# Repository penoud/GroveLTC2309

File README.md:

# GroveLTC2309
A Grove i2c 8 channels ADC ŵith amplifier for each channel

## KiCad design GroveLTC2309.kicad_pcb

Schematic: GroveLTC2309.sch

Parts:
P1, P2, P3, P4, P5, P6, P7, P8, P9: CONN_4_GROVE
R29, R30, R31, R32: 4.7K

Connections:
+5V: P1.3, P2.3, P3.3, P4.3, P5.3, P6.3, P7.3, P8.3, P9.3, R29.1, R30.1, R31.1, R32.1; also elsewhere on the board
/ADC/SCL: R32.2; also elsewhere on the board
/ADC/SDA: R31.2; also elsewhere on the board
/Amplifier1/IN0: P1.1; also elsewhere on the board
/Amplifier1/IN1: P2.1; also elsewhere on the board
/Amplifier1/IN2: P3.1; also elsewhere on the board
/Amplifier1/IN3: P4.1; also elsewhere on the board
/Amplifier2/IN0: P5.1; also elsewhere on the board
/Amplifier2/IN1: P6.1; also elsewhere on the board
/Amplifier2/IN2: P7.1; also elsewhere on the board
/Amplifier2/IN3: P8.1; also elsewhere on the board
/TCA9517A/SCL_B: P9.1, R29.2; also elsewhere on the board
/TCA9517A/SDA_B: P9.2, R30.2; also elsewhere on the board
GND: P1.4, P2.4, P3.4, P4.4, P5.4, P6.4, P7.4, P8.4, P9.4; also elsewhere on the board

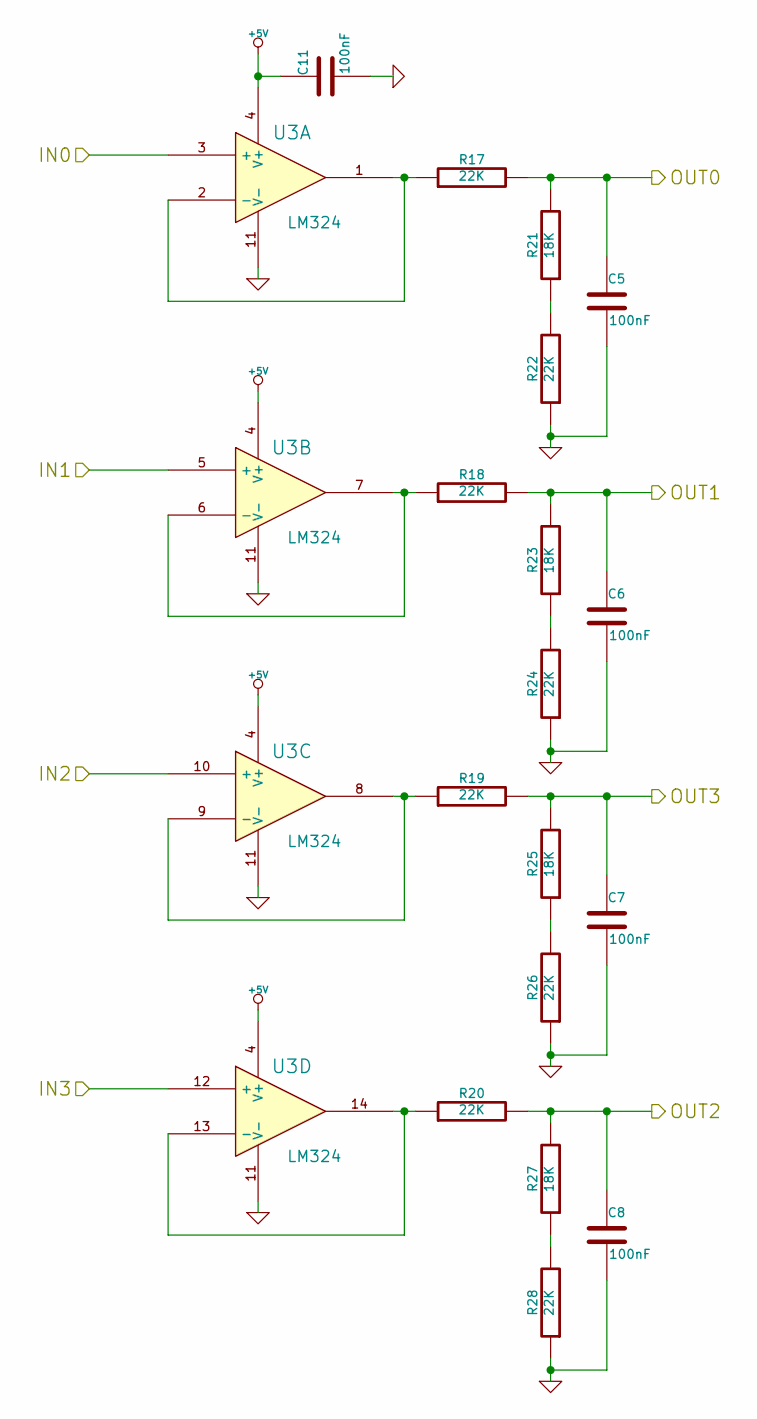
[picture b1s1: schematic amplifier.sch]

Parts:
C1, C2, C3, C4, C9: 100nF
R1, R2, R3, R4, R6, R8, R10, R12: 22K
R5, R7, R9, R11: 18K
U1: LM324

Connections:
+5V: C9.1, U1.4 (V+); also elsewhere on the board
/ADC/CH4: C1.1, R1.2, R5.2; also elsewhere on the board
/ADC/CH5: C2.1, R2.2, R7.2; also elsewhere on the board
/ADC/CH6: C4.1, R4.2, R11.2; also elsewhere on the board
/ADC/CH7: C3.1, R3.2, R9.2; also elsewhere on the board
/Amplifier2/IN0: U1.3 (+); also elsewhere on the board
/Amplifier2/IN1: U1.5 (+); also elsewhere on the board
/Amplifier2/IN2: U1.10 (+); also elsewhere on the board
/Amplifier2/IN3: U1.12 (+); also elsewhere on the board
GND: C1.2, C2.2, C3.2, C4.2, C9.2, R6.1, R8.1, R10.1, R12.1, U1.11 (V-); also elsewhere on the board
unnamed: R3.1, U1.8, U1.9 (-)
unnamed: R9.1, R10.2
unnamed: R4.1, U1.13 (-), U1.14
unnamed: R11.1, R12.2
unnamed: R5.1, R6.2
unnamed: R2.1, U1.6 (-), U1.7
unnamed: R1.1, U1.1, U1.2 (-)
unnamed: R7.1, R8.2

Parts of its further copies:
C5, C8, C11: 100nF
R17, R18, R19, R20, R22, R24, R26, R28: 22K
R21, R23, R25, R27: 18K
U3: LM324

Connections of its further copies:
+5V: C11.1, U3.4 (V+); also elsewhere on the board
/ADC/CH0: C5.1, R17.2, R21.2; also elsewhere on the board
/ADC/CH1: R18.2, R23.2; also elsewhere on the board
/ADC/CH2: C8.1, R20.2, R27.2; also elsewhere on the board
/ADC/CH3: R19.2, R25.2; also elsewhere on the board
/Amplifier1/IN0: U3.3 (+); also elsewhere on the board
/Amplifier1/IN1: U3.5 (+); also elsewhere on the board
/Amplifier1/IN2: U3.10 (+); also elsewhere on the board
/Amplifier1/IN3: U3.12 (+); also elsewhere on the board
GND: C5.2, C8.2, C11.2, R22.1, R24.1, R26.1, R28.1, U3.11 (V-); also elsewhere on the board
unnamed: R19.1, U3.8, U3.9 (-)
unnamed: R25.1, R26.2
unnamed: R20.1, U3.13 (-), U3.14
unnamed: R27.1, R28.2
unnamed: R21.1, R22.2
unnamed: R18.1, U3.6 (-), U3.7
unnamed: R17.1, U3.1, U3.2 (-)
unnamed: R23.1, R24.2

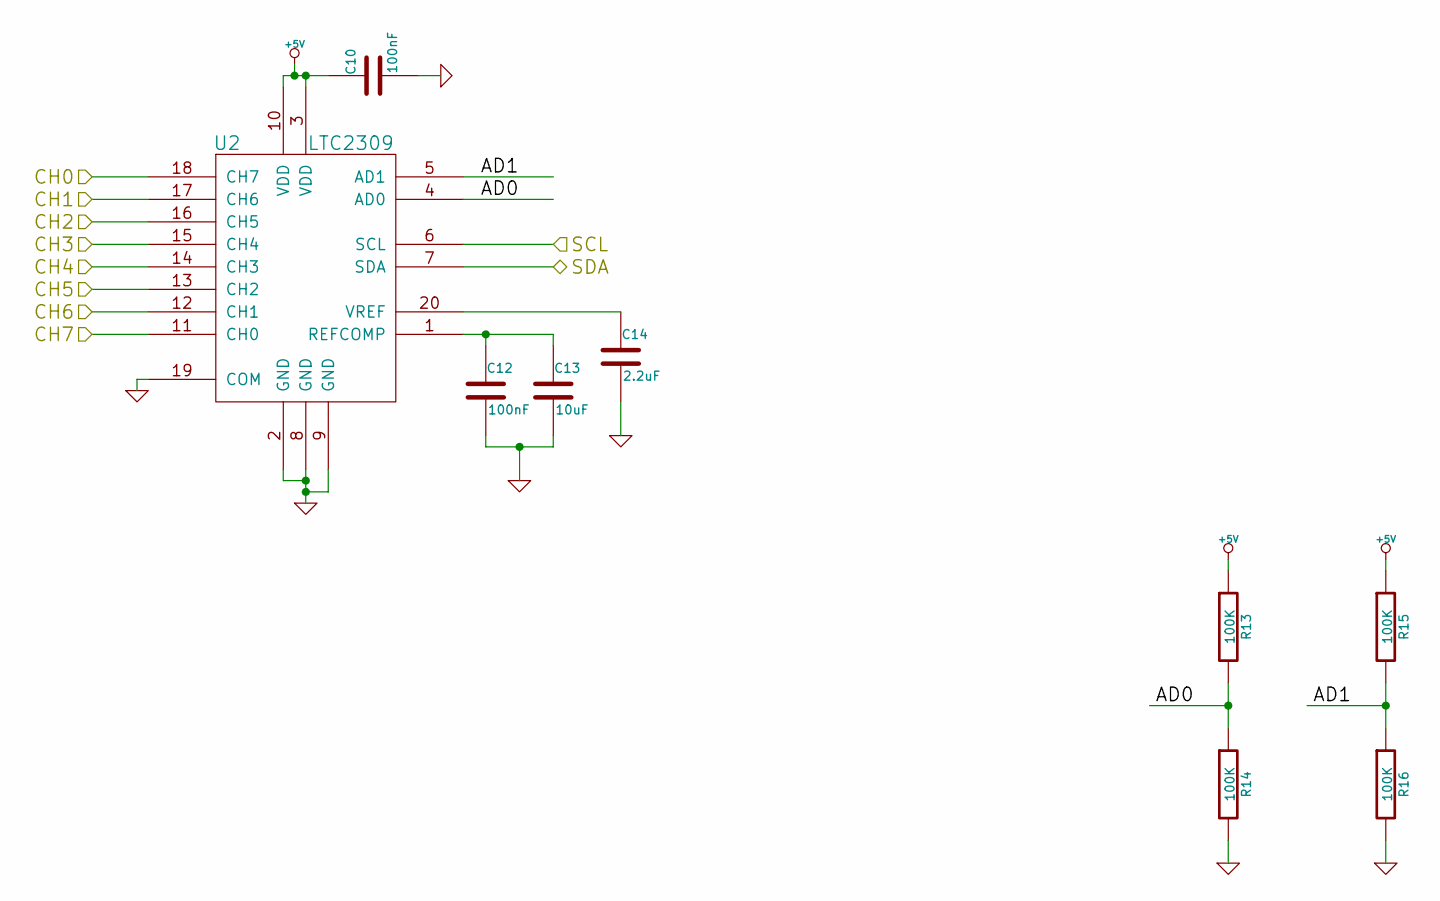
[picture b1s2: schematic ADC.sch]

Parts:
C10, C12: 100nF
C13: 10uF
C14: 2.2uF
R13, R14, R15, R16: 100K
U2: LTC2309

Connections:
+5V: C10.1, R13.1, R15.1, U2.3 (VDD), U2.10 (VDD); also elsewhere on the board
/ADC/AD0: R13.2, R14.1, U2.4 (AD0)
/ADC/AD1: R15.2, R16.1, U2.5 (AD1)
/ADC/CH0: U2.18 (CH7); also elsewhere on the board
/ADC/CH1: U2.17 (CH6); also elsewhere on the board
/ADC/CH2: U2.16 (CH5); also elsewhere on the board
/ADC/CH3: U2.15 (CH4); also elsewhere on the board
/ADC/CH4: U2.14 (CH3); also elsewhere on the board
/ADC/CH5: U2.13 (CH2); also elsewhere on the board
/ADC/CH6: U2.12 (CH1); also elsewhere on the board
/ADC/CH7: U2.11 (CH0); also elsewhere on the board
/ADC/SCL: U2.6 (SCL); also elsewhere on the board
/ADC/SDA: U2.7 (SDA); also elsewhere on the board
GND: C10.2, C12.2, C13.2, C14.2, R14.2, R16.2, U2.2 (GND), U2.8 (GND), U2.9 (GND), U2.19 (COM); also elsewhere on the board
unnamed: C14.1, U2.20 (VREF)
unnamed: C12.1, C13.1, U2.1 (REFCOMP)

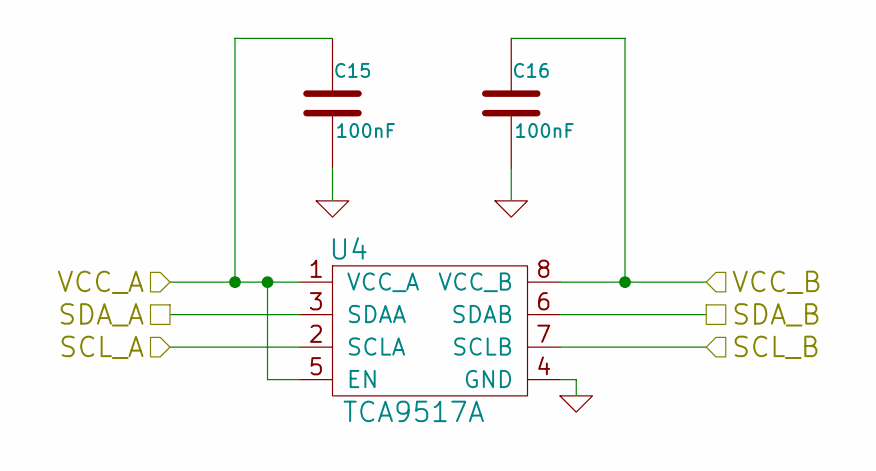
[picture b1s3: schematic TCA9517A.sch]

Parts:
C15, C16: 100nF
U4: TCA9517A

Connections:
+5V: C15.1, C16.1, U4.1 (VCC_A), U4.5 (EN), U4.8 (VCC_B); also elsewhere on the board
/ADC/SCL: U4.2 (SCLA); also elsewhere on the board
/ADC/SDA: U4.3 (SDAA); also elsewhere on the board
/TCA9517A/SCL_B: U4.7 (SCLB); also elsewhere on the board
/TCA9517A/SDA_B: U4.6 (SDAB); also elsewhere on the board
GND: C15.2, C16.2, U4.4 (GND); also elsewhere on the board

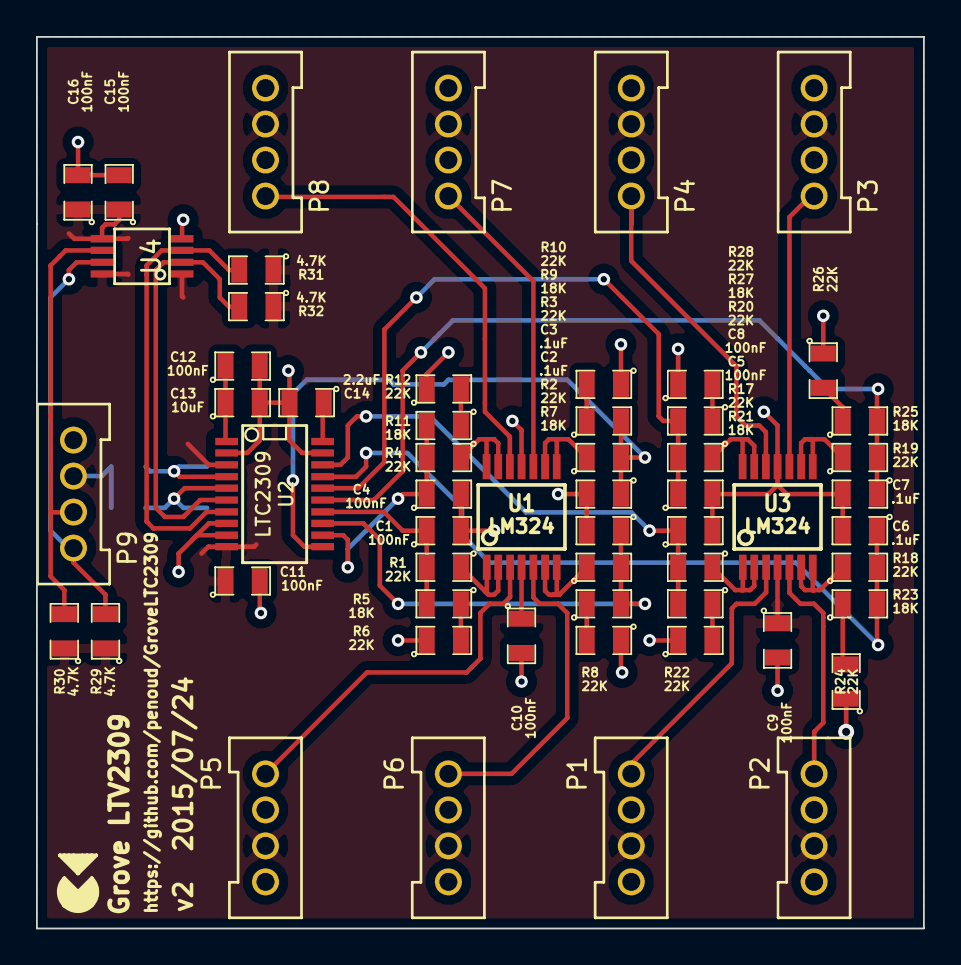
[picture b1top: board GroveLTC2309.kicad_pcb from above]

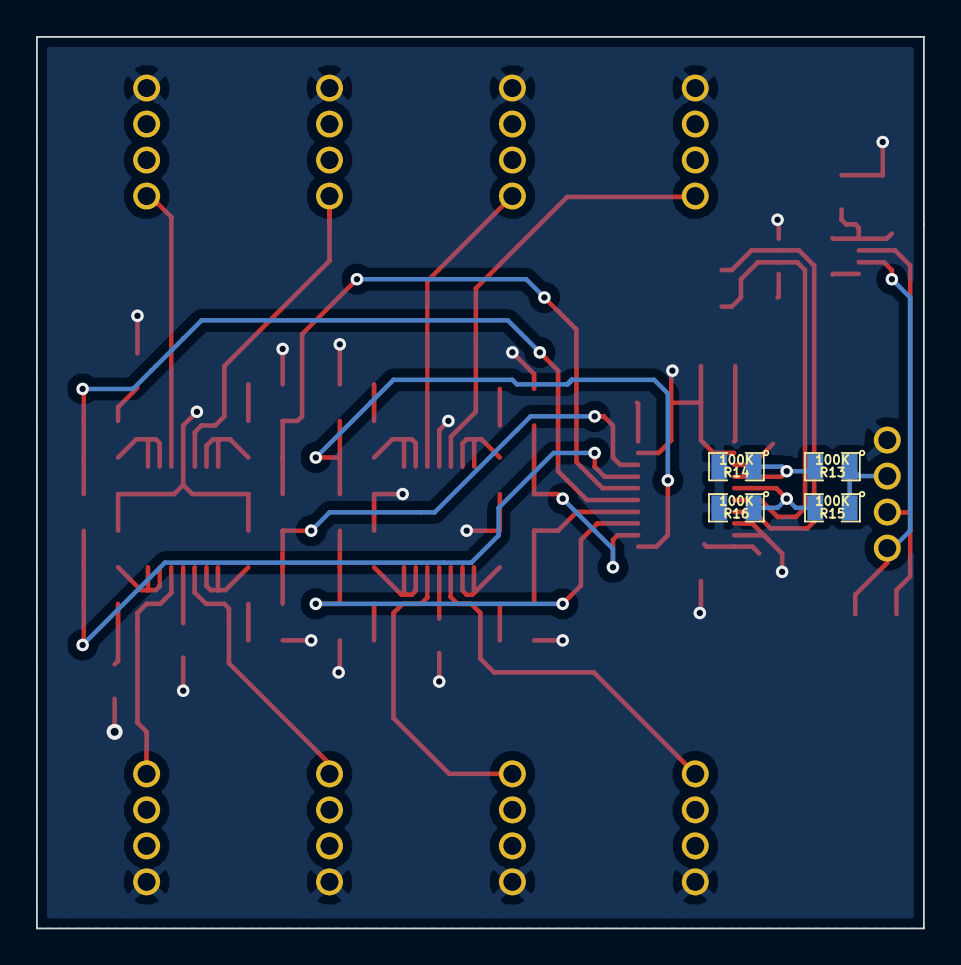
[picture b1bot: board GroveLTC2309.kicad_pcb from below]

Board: 2 copper layers, 49.3 x 49.5 mm, 61 parts (4 on the bottom side), 42 nets.

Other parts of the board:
C6, C7: .1uF; SM0805

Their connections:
/ADC/CH1: C6.1; also elsewhere on the board
/ADC/CH3: C7.1; also elsewhere on the board
GND: C6.2, C7.2; also elsewhere on the board

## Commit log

2015-07-17 initial revision
2015-07-28 version change to 2, first trial for layout revue
2015-07-28 add pdf schematic
2015-07-28 add gerber
